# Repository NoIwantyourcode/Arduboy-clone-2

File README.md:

# Arduboy-clone

This is a clone of a popular Arduino based, Gameboy style console known as the Arduboy!

# Why I made this

I have always wanted a game console, But my parents have never let me have one, Instead wanting to me to focus on my studies, So I decided to make this as a more clever rebellion (Don't worry, I asked them before designing this)

# Schematic Pictures

# PCB Routed pictures

# PCB rendered pictures

# Case pictures

# Assembled pictures

# IRL pictures:

# Demo video

Here is the demo video link [https://youtube.com/shorts/noF8kV4LzxU?feature=shared](https://youtube.com/shorts/noF8kV4LzxU?feature=shared)
Heres the second demo video (with case) [https://youtube.com/shorts/UJCODutgSrg?si=xlWPpG5ztKTAeB8U](https://youtube.com/shorts/UJCODutgSrg?si=xlWPpG5ztKTAeB8U)

# Notes

Sadly this project does not work

this project uses firmware that is not mine, it uses the very popular cathy3k bootloader by MrBlinky, here is the link to the firmwares github: [https://github.com/MrBlinky/cathy3k]

and planned to test the project through games found here: [https://community.arduboy.com/c/games/35]

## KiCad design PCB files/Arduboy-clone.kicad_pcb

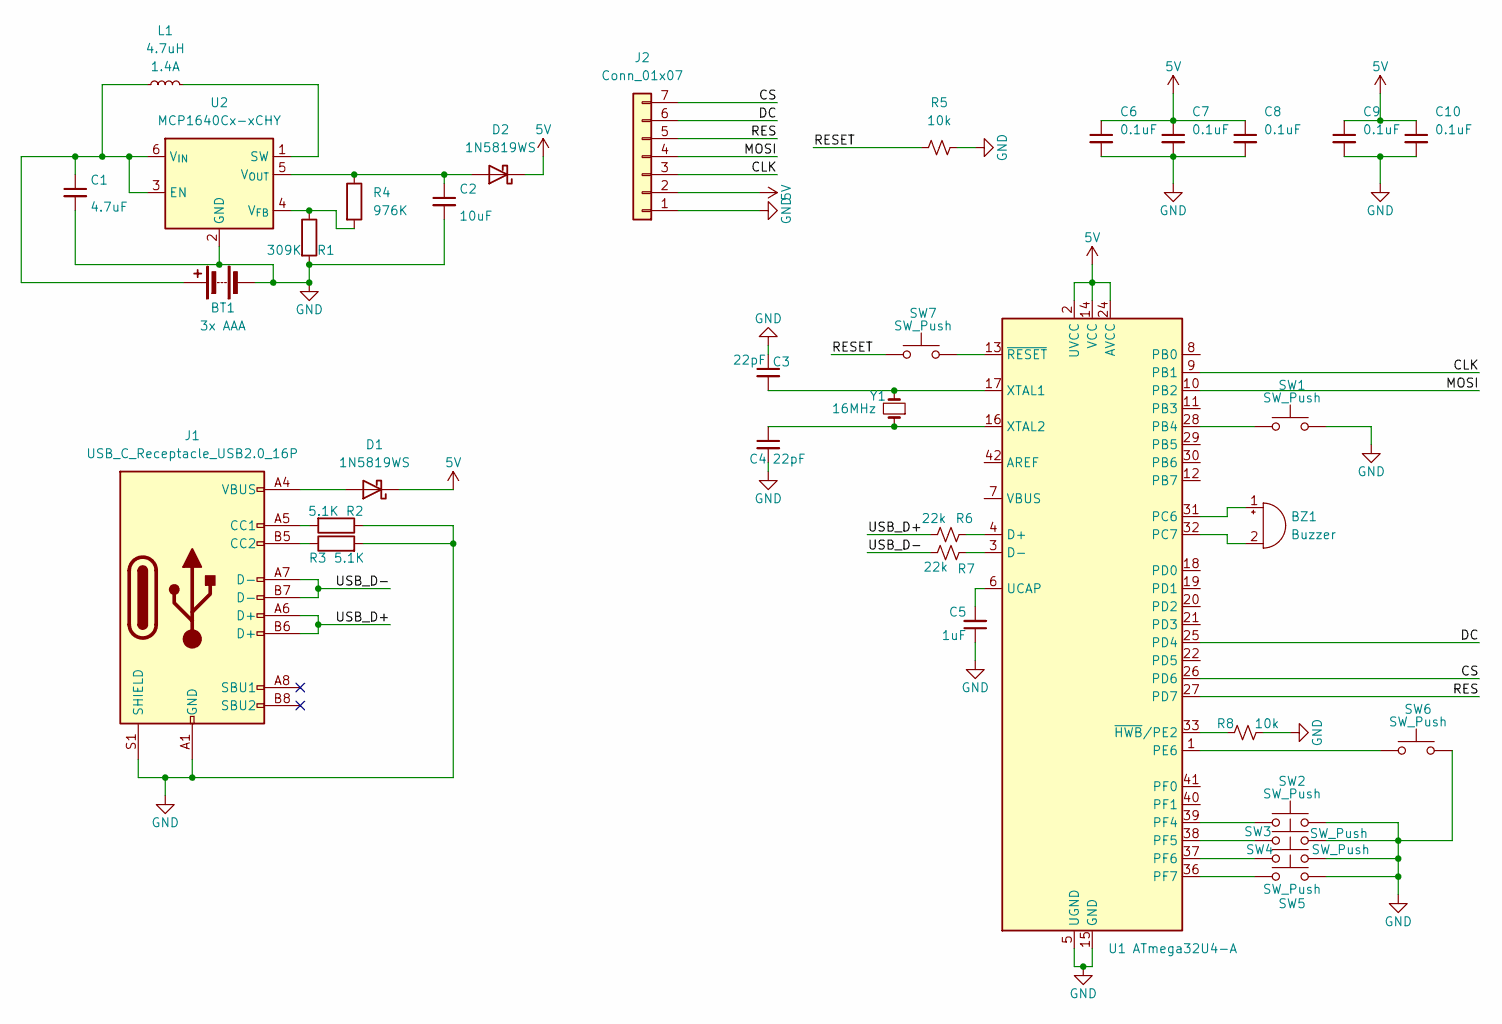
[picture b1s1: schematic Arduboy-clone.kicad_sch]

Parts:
BT1: 3x AAA; BatteryHolder_Keystone_2468_2xAAA
BZ1: Buzzer; Buzzer_Murata_PKLCS1212E
C1: 4.7uF; C_0603_1608Metric; Voltage 1kV; Tolerance 100%
C2: 10uF; C_0603_1608Metric; Voltage 1kV; Tolerance 100%
C3, C4: 22pF; C_0603_1608Metric; Voltage 1kV; Tolerance 100%
C5: 1uF; C_0201_0603Metric; Voltage 16V; Tolerance 10%
C6, C7, C8, C9, C10: 0.1uF; C_0201_0603Metric; Voltage 16V; Tolerance 10%
D1, D2: 1N5819WS; D_SOD-323
J1: USB_C_Receptacle_USB2.0_16P; USB_C_Receptacle_HCTL_HC-TYPE-C-16P-01A
J2: Conn_01x07; PinHeader_1x07_P2.54mm_Vertical
L1: 4.7uH; 1008_2520Metric
R1: 309K; C_0603_1608Metric
R2, R3: 5.1K; C_0402_1005Metric
R4: 976K; C_0603_1608Metric
R5, R8: 10k; R_0402_1005Metric
R6, R7: 22k; R_0402_1005Metric
SW1, SW2, SW3, SW4, SW5, SW6, SW7: SW_Push; SW_PUSH_6mm
U1: ATmega32U4-A; TQFP-44_10x10mm_P0.8mm
U2: MCP1640Cx-xCHY; SOT-23-6
Y1: 16MHz; Crystal_SMD_2.0x1.6mm

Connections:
5V: C6.1, C7.1, C8.1, C9.1, C10.1, D1.1 (K), D2.1 (K), J2.2, U1.2 (UVCC), U1.14 (VCC), U1.24 (AVCC), U1.34 (VCC), U1.44 (AVCC)
/CLK: J2.3, U1.9 (PB1)
/CS: J2.7, U1.26 (PD6)
/DC: J2.6, U1.25 (PD4)
/MOSI: J2.4, U1.10 (PB2)
/RES: J2.5, U1.27 (PD7)
/RESET: R5.1, SW7.1
/USB_D+: J1.A6 (D+), J1.B6 (D+), R6.1
/USB_D-: J1.A7 (D-), J1.B7 (D-), R7.1
GND: BT1.2 (-), C1.2, C2.2, C3.1, C4.2, C5.1, C6.2, C7.2, C8.2, C9.2, C10.2, J1.A1 (GND), J1.A12 (GND), J1.B1 (GND), J1.B12 (GND), J1.S1 (SHIELD), J2.1, R1.2, R2.1, R3.2, R5.2, R8.2, SW1.2, SW2.2, SW3.2, SW4.2, SW5.2, SW6.2, U1.5 (UGND), U1.15 (GND), U1.23 (GND), U1.35 (GND), U1.43 (GND), U2.2 (GND)
unnamed: BT1.1 (+), C1.1, L1.1, U2.3 (EN), U2.6 (V_{IN})
unnamed: BZ1.1 (+), U1.31 (PC6)
unnamed: BZ1.2 (-), U1.32 (PC7)
unnamed: D1.2 (A), J1.A4 (VBUS), J1.A9 (VBUS), J1.B4 (VBUS), J1.B9 (VBUS)
unnamed: C2.1, D2.2 (A), R4.1, U2.5 (V_{OUT})
unnamed: J1.A5 (CC1), R2.2
unnamed: J1.B5 (CC2), R3.1
unnamed: R6.2, U1.4 (D+)
unnamed: R7.2, U1.3 (D-)
unnamed: SW1.1, U1.28 (PB4)
unnamed: SW6.1, U1.1 (PE6)
unnamed: SW2.1, U1.39 (PF4)
unnamed: SW3.1, U1.38 (PF5)
unnamed: SW4.1, U1.37 (PF6)
unnamed: SW5.1, U1.36 (PF7)
unnamed: C5.2, U1.6 (UCAP)
unnamed: C3.2, U1.17 (XTAL1), Y1.2
unnamed: C4.1, U1.16 (XTAL2), Y1.1
unnamed: R8.1, U1.33 (~HWB/PE2)
unnamed: SW7.2, U1.13 (~RESET)
unnamed: L1.2, U2.1 (SW)
unnamed: R1.1, R4.2, U2.4 (V_{FB})

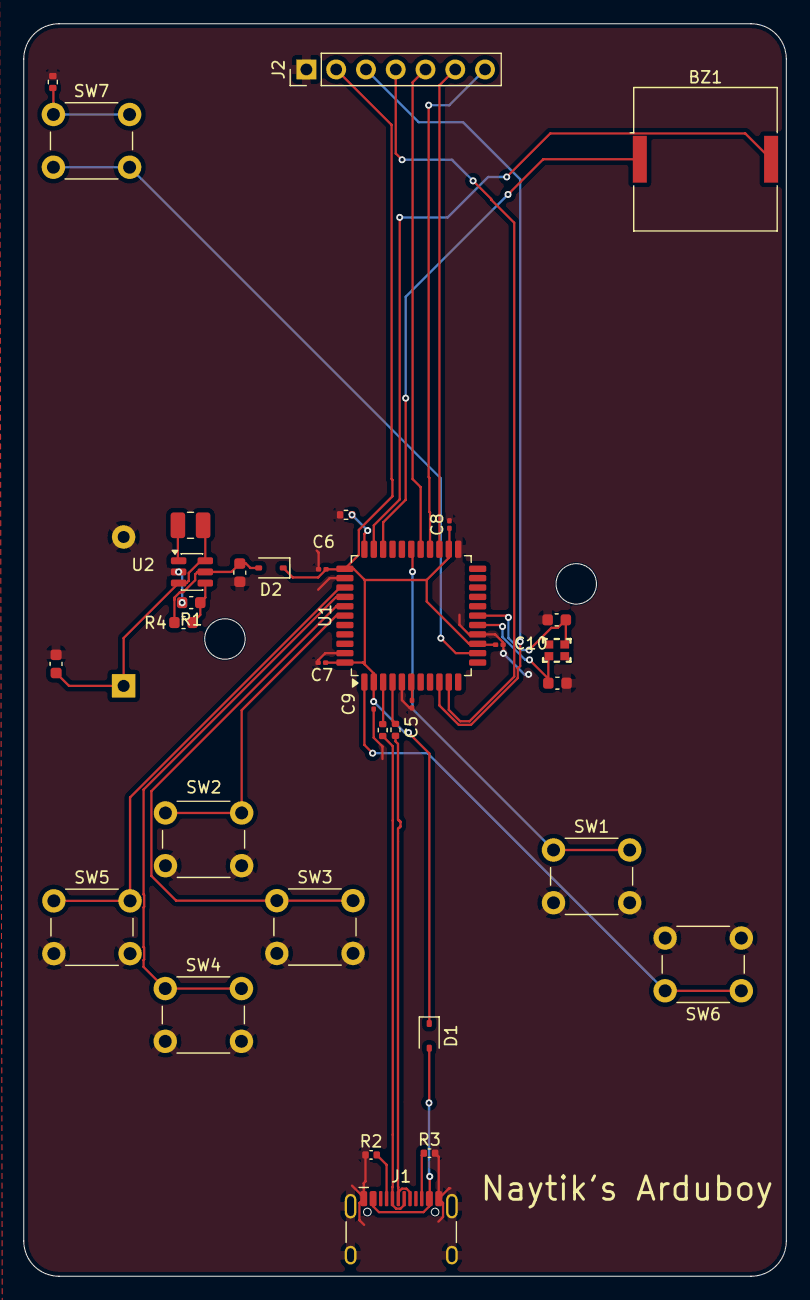
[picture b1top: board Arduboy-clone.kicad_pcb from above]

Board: 2 copper layers, 65.1 x 106.8 mm, 35 parts (1 on the bottom side), 32 nets.

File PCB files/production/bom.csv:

Designator,Footprint,Quantity,Value,LCSC Part #
BT1,BatteryHolder_Keystone_2468_2xAAA,1,3x AAA,
BZ1,Buzzer_Murata_PKLCS1212E,1,Buzzer,
C1,0603,1,4.7uF,
"C10, C6, C7, C8, C9",0201,5,0.1uF,
C2,0603,1,10uF,
"C3, C4",0603,2,22pF,
C5,0201,1,1uF,
"D1, D2",D_SOD-323,2,1N5819WS,
J1,USB_C_Receptacle_HCTL_HC-TYPE-C-16P-01A,1,USB_C_Receptacle_USB2.0_16P,
J2,PinHeader_1x07_P2.54mm_Vertical,1,Conn_01x07,
L1,1008_2520Metric,1,4.7uH,
R1,0603,1,309K,
"R2, R3",0402,2,5.1K,
R4,0603,1,976K,
"R5, R8",0402,2,10k,
"R6, R7",0402,2,22k,
"SW1, SW2, SW3, SW4, SW5, SW6, SW7",SW_PUSH_6mm,7,SW_Push,
U1,TQFP-44_10x10mm_P0.8mm,1,ATmega32U4-A,
U2,SOT-23-6,1,MCP1640Cx-xCHY,
Y1,Crystal_SMD_2.0x1.6mm,1,16MHz,

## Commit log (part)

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2026-05-23 Added MPU, Display and Decoupling Capacitors
2026-05-23 Update JOURNAL.md with recent hardware additions
    Documented the addition of MPU, display, buttons, and capacitors.
2026-05-24 added display header
2026-05-24 added power circuit, display, USB-C circuits
    I added the rest of the circuit and completed the whole schematic
2026-05-24 Completely routed the board
2026-05-24 Generated Gerber File
2026-05-24 Added Bom file and replaced display with a cheaper alternative
2026-05-24 Organized all the files into their respective folders
2026-05-24 Added silkscreen customization
2026-05-24 Added bom... again
2026-05-24 Added bottom case
    I will add topcase after I get the PCB because I need accurate measurements
2026-05-24 added top case
2026-05-25 added better case
2026-05-25 updated bom
2026-05-26 added USB port
2026-05-26 changed Battery from AAA to LiPo (no case difference yet)
2026-05-26 Added TP4056 charging board
2026-05-27 added hole for speaker
2026-06-02 added keycaps
2026-06-02 added custom buttom tops
2026-06-08 Added extra images
2026-06-08 Added silkscreen art
2026-06-08 random
